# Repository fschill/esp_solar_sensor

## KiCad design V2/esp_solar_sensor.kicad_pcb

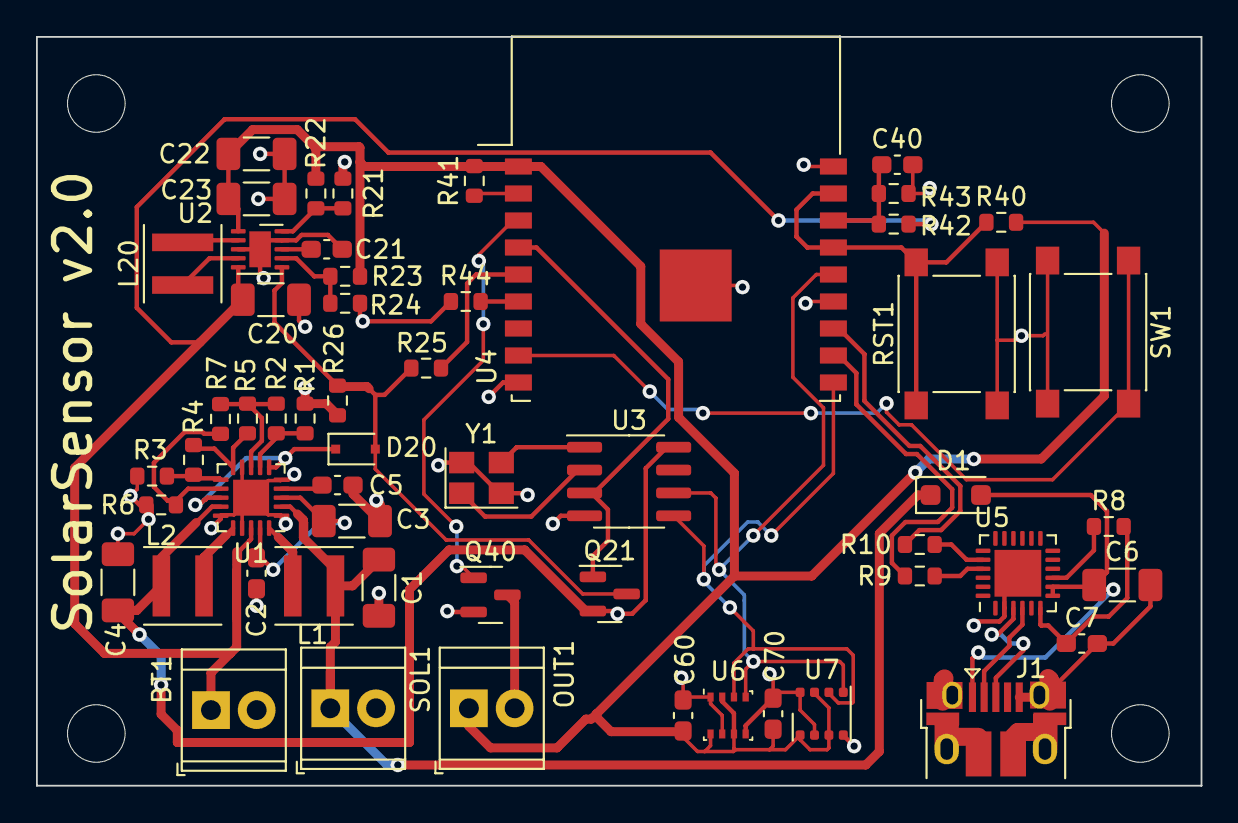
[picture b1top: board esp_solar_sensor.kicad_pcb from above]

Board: 2 copper layers, 64.7 x 41.6 mm, 60 parts (0 on the bottom side), 43 nets.

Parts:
BT1: Battery_Cell; TerminalBlock_TE_282834-2_1x02_P2.54mm_Horizontal
C1, C3, C4, C6, C20: 10uF; C_1206_3216Metric_Pad1.33x1.80mm_HandSolder
C2, C5: 10nF; C_0603_1608Metric_Pad1.08x0.95mm_HandSolder
C7, C21, C40, C60, C70: 100nF; C_0603_1608Metric_Pad1.08x0.95mm_HandSolder
C22, C23: 22uF; C_1206_3216Metric_Pad1.33x1.80mm_HandSolder
D1: PMEG6010CEH; D_SOD-123F
D20: PMEG4005CEJ; D_SOD-323F
H1, H2, H3, H4: MountingHole_Pad; MountingHole_3.2mm_M3
J1: USB_B_Micro; USB_Micro-B_Amphenol_10103594-0001LF_Horizontal
L1: 22uH; L_Coilcraft_XxL4040
L2: 10uH; L_Coilcraft_XxL4040
L20: 2.2uH; L_Coilcraft_XxL4040
OUT1: Screw_Terminal_01x02; TerminalBlock_TE_282834-2_1x02_P2.54mm_Horizontal
Q21: AO3401A; SOT-23
Q40: AO3400A; SOT-23
R1, R3: 5.62M; R_0603_1608Metric
R2: 7.32M; R_0603_1608Metric
R4: 5.49M; R_0603_1608Metric
R5: 154k; R_0603_1608Metric
R6: 4.7M; R_0603_1608Metric
R7: 8.2M; R_0603_1608Metric
R8, R24, R25: 1k; R_0603_1608Metric
R9, R10: 2.2k; R_0603_1608Metric
R21: 180k; R_0603_1608Metric
R22: 1M; R_0603_1608Metric
R23, R26: DNC; R_0603_1608Metric
R40, R41, R44: 10k; R_0603_1608Metric
R42: 820k; R_0603_1608Metric
R43: 220k; R_0603_1608Metric
RST1: SW_Push; SW_Push_1P1T_NO_6x6mm_H9.5mm
SOL1: Screw_Terminal_01x02; TerminalBlock_TE_282834-2_1x02_P2.54mm_Horizontal
SW1: SW_Push; SW_Push_1P1T_NO_6x6mm_H9.5mm
U1: BQ25570; QFN-20-1EP_3.5x3.5mm_P0.5mm_EP2x2mm
U2: TPS63030DSK; WSON-10-1EP_2.5x2.5mm_P0.5mm_EP1.2x2mm
U3: PCF8563T; SOIC-8_3.9x4.9mm_P1.27mm
U4: ESP-WROOM-02
U5: CP2102N-Axx-xQFN24; QFN-24-1EP_4x4mm_P0.5mm_EP2.6x2.6mm
U6: BME280; Bosch_LGA-8_2.5x2.5mm_P0.65mm_ClockwisePinNumbering
U7: BME680; Bosch_LGA-8_3x3mm_P0.8mm_ClockwisePinNumbering
Y1: Crystal_GND24; Crystal_SMD_3225-4Pin_3.2x2.5mm

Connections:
+3.3VP: C4.1, L2.2, Q21.2 (S), U1.14 (VOUT), U3.8 (VDD)
+3V3: C22.1, C23.1, C60.1, C70.1, OUT1.1, R22.1, R23.1, R40.2, R41.2, U2.1 (VOUT), U4.1 (VDD), U6.2 (CSB), U6.6 (VDDIO), U6.8 (VDD), U7.2 (CSB), U7.6 (VDDIO), U7.8 (VDD)
/RST: R40.1, RST1.1, U4.15 (RST), U4.17 (IO16)
/SCL: U3.6 (SCL), U4.14 (IO5), U6.4 (SCK), U7.4 (SCK)
/SDA: U3.5 (SDA), U4.10 (IO4), U6.3 (SDI), U7.3 (SDI)
/VBAT_OK: D20.1 (K), U1.6 (VOUT_EN), U1.13 (VBAT_OK)
ESP_RXD: R9.2, U4.11 (RXD)
ESP_TXD: R10.2, U4.12 (TXD)
GND: BT1.2 (-), C1.2, C2.2, C3.2, C4.2, C5.2, C6.2, C7.2, C20.2, C21.2, C22.2, C23.2, C40.2, C60.2, C70.2, J1.5 (GND), J1.6 (Shield), Q40.2 (S), R1.2, R3.2, R6.2, R21.2, R24.2, R26.2, R43.1, R44.1, RST1.2, SOL1.2, SW1.2, U1.1 (VSS), U1.5 (~EN), U1.9 (VSS), U1.15 (VSS), U1.17 (VSS), U1.21 (VSS), U2.3 (PGND), U2.9 (GND), U2.11 (PGND), U3.4 (VSS), U4.9 (GND), U4.13 (GND), U4.18 (GND), U4.19 (GND), U5.2 (GND), U5.25 (GND), U6.1 (GND), U6.5 (SDO), U6.7 (GND), U7.1 (GND), U7.5 (SDO), U7.7 (GND), Y1.2, Y1.4
unnamed: C6.1, D1.2 (A), J1.1 (VBUS), U5.7 (VREGIN), U5.8 (VBUS)
unnamed: J1.3 (D+), U5.3 (D+)
unnamed: J1.2 (D-), U5.4 (D-)
unnamed: OUT1.2, Q40.3 (D)
unnamed: Q40.1 (G), U4.3 (IO14)
unnamed: L1.2, U1.20 (LBOOST)
unnamed: L2.1, U1.16 (LBUCK)
unnamed: R4.2, R5.1, U1.10 (OK_HYST)
unnamed: R3.1, R4.1, U1.11 (OK_PROG)
unnamed: R1.1, R2.2, U1.7 (VBAT_OV)
unnamed: C2.1, C3.1, U1.3 (VOC_SAMP), U1.19 (VSTOR)
unnamed: R6.1, R7.2, U1.12 (VOUT_SET)
unnamed: R2.1, R5.2, R7.1, U1.8 (VRDIV)
unnamed: C5.1, U1.4 (VREF_SAMP)
unnamed: R21.1, R22.2, U2.10 (FB)
unnamed: L20.1, U2.4 (L1)
unnamed: L20.2, U2.2 (L2)
unnamed: C21.1, U2.8 (VINA)
unnamed: U3.1 (OSCI), Y1.3
unnamed: U3.2 (OSCO), Y1.1
unnamed: R41.1, U4.2 (EN)
unnamed: SW1.1, U4.8 (IO0)
unnamed: R44.2, U4.6 (IO15)
unnamed: C40.1, R42.1, R43.2, U4.16 (TOUT)
unnamed: R10.1, U5.20 (RXD)
unnamed: R9.1, U5.21 (TXD)
unnamed: C7.1, R8.2, U5.6 (VDD)
unnamed: R8.1, U5.9 (~RST)
POWER_EN: R25.1, U4.5 (IO13)
PSAVE: R23.2, R24.1, U2.7 (PS/SYNC)
SOLAR_IN: C1.1, D1.1 (K), L1.1, SOL1.1, U1.2 (VIN_DC)
VDC: BT1.1 (+), C20.1, R42.2, U1.18 (VBAT), U2.5 (VIN)
V_EN: D20.2 (A), Q21.3 (D), R25.2, R26.1, U2.6 (EN)
_RTC_ALERT: Q21.1 (G), U3.3 (~INT), U4.4 (IO12)

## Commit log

2024-09-06 initial add and commit
2024-09-06 add LICENSE
